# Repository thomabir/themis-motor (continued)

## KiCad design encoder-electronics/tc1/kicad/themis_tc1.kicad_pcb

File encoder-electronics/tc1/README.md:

# Themis TC1

Goal: Figure out whether 10 kHz amplitude modulaiton works with the AD9834 DDS via the FS_ADJUST pin.

Secondary goal (optional): Have a minimal "sender" circuit for the encoder, test the differential driver

- Interfaces:
  - Power in: 4V lab PSU, ±13V lab PSU
  - Signal out: differential amplified DDS signal, can power the existing encoder coils
  - Digital IO: Every useful digital pin from the DDS is accessible via a pin header, for easy debugging
  - Testpoints: Every single analog signal is accessible, and jumpers between main sections are used for easy disconnecting of blocks.

- Strategy
  - Passives: Use 0Ωs and DNPs to keep it flexible. 0805 everything for easy modification by hand.
  - Using screw terminals for power and encoder, pin headers for digital. Not fancy, but cheap and quick.

- Power:
  - ±12 V: LT3097
    - 10 CHF/pc (= 5 CHF/rail)
    - 500 mA bipolar adjustable ultra-low-noise LDO
    - It's the best. Slightly pricy, but just works, no fuss.
    - Basically excludes LDOs as a noise source -> faster prototyping.
    - (Hurts a bit to buy fancy parts for a prototype)
  - 3.3 V: MAX8887
    - I've used it before -> copy-paste design
    - Decently low-noise
- DDS: AD9834
  - The big unknown: Can it modulate quickly and with low noise?
  - Does the differential output work as expected?
  - How to program it? Will figure out once I get it
- Clock: Active crystal oscillator at 75 MHz
- Diff-amp to drive encoder: AD8390
  - Lots of power, cheap, fast
  - Unknown: Made for ADSL, let's see if this works well in this application? Spec wise, it should work.

## How to run

Upload code to Teensy: `~/.platformio/penv/bin/pio run -e teensy41 -t upload`

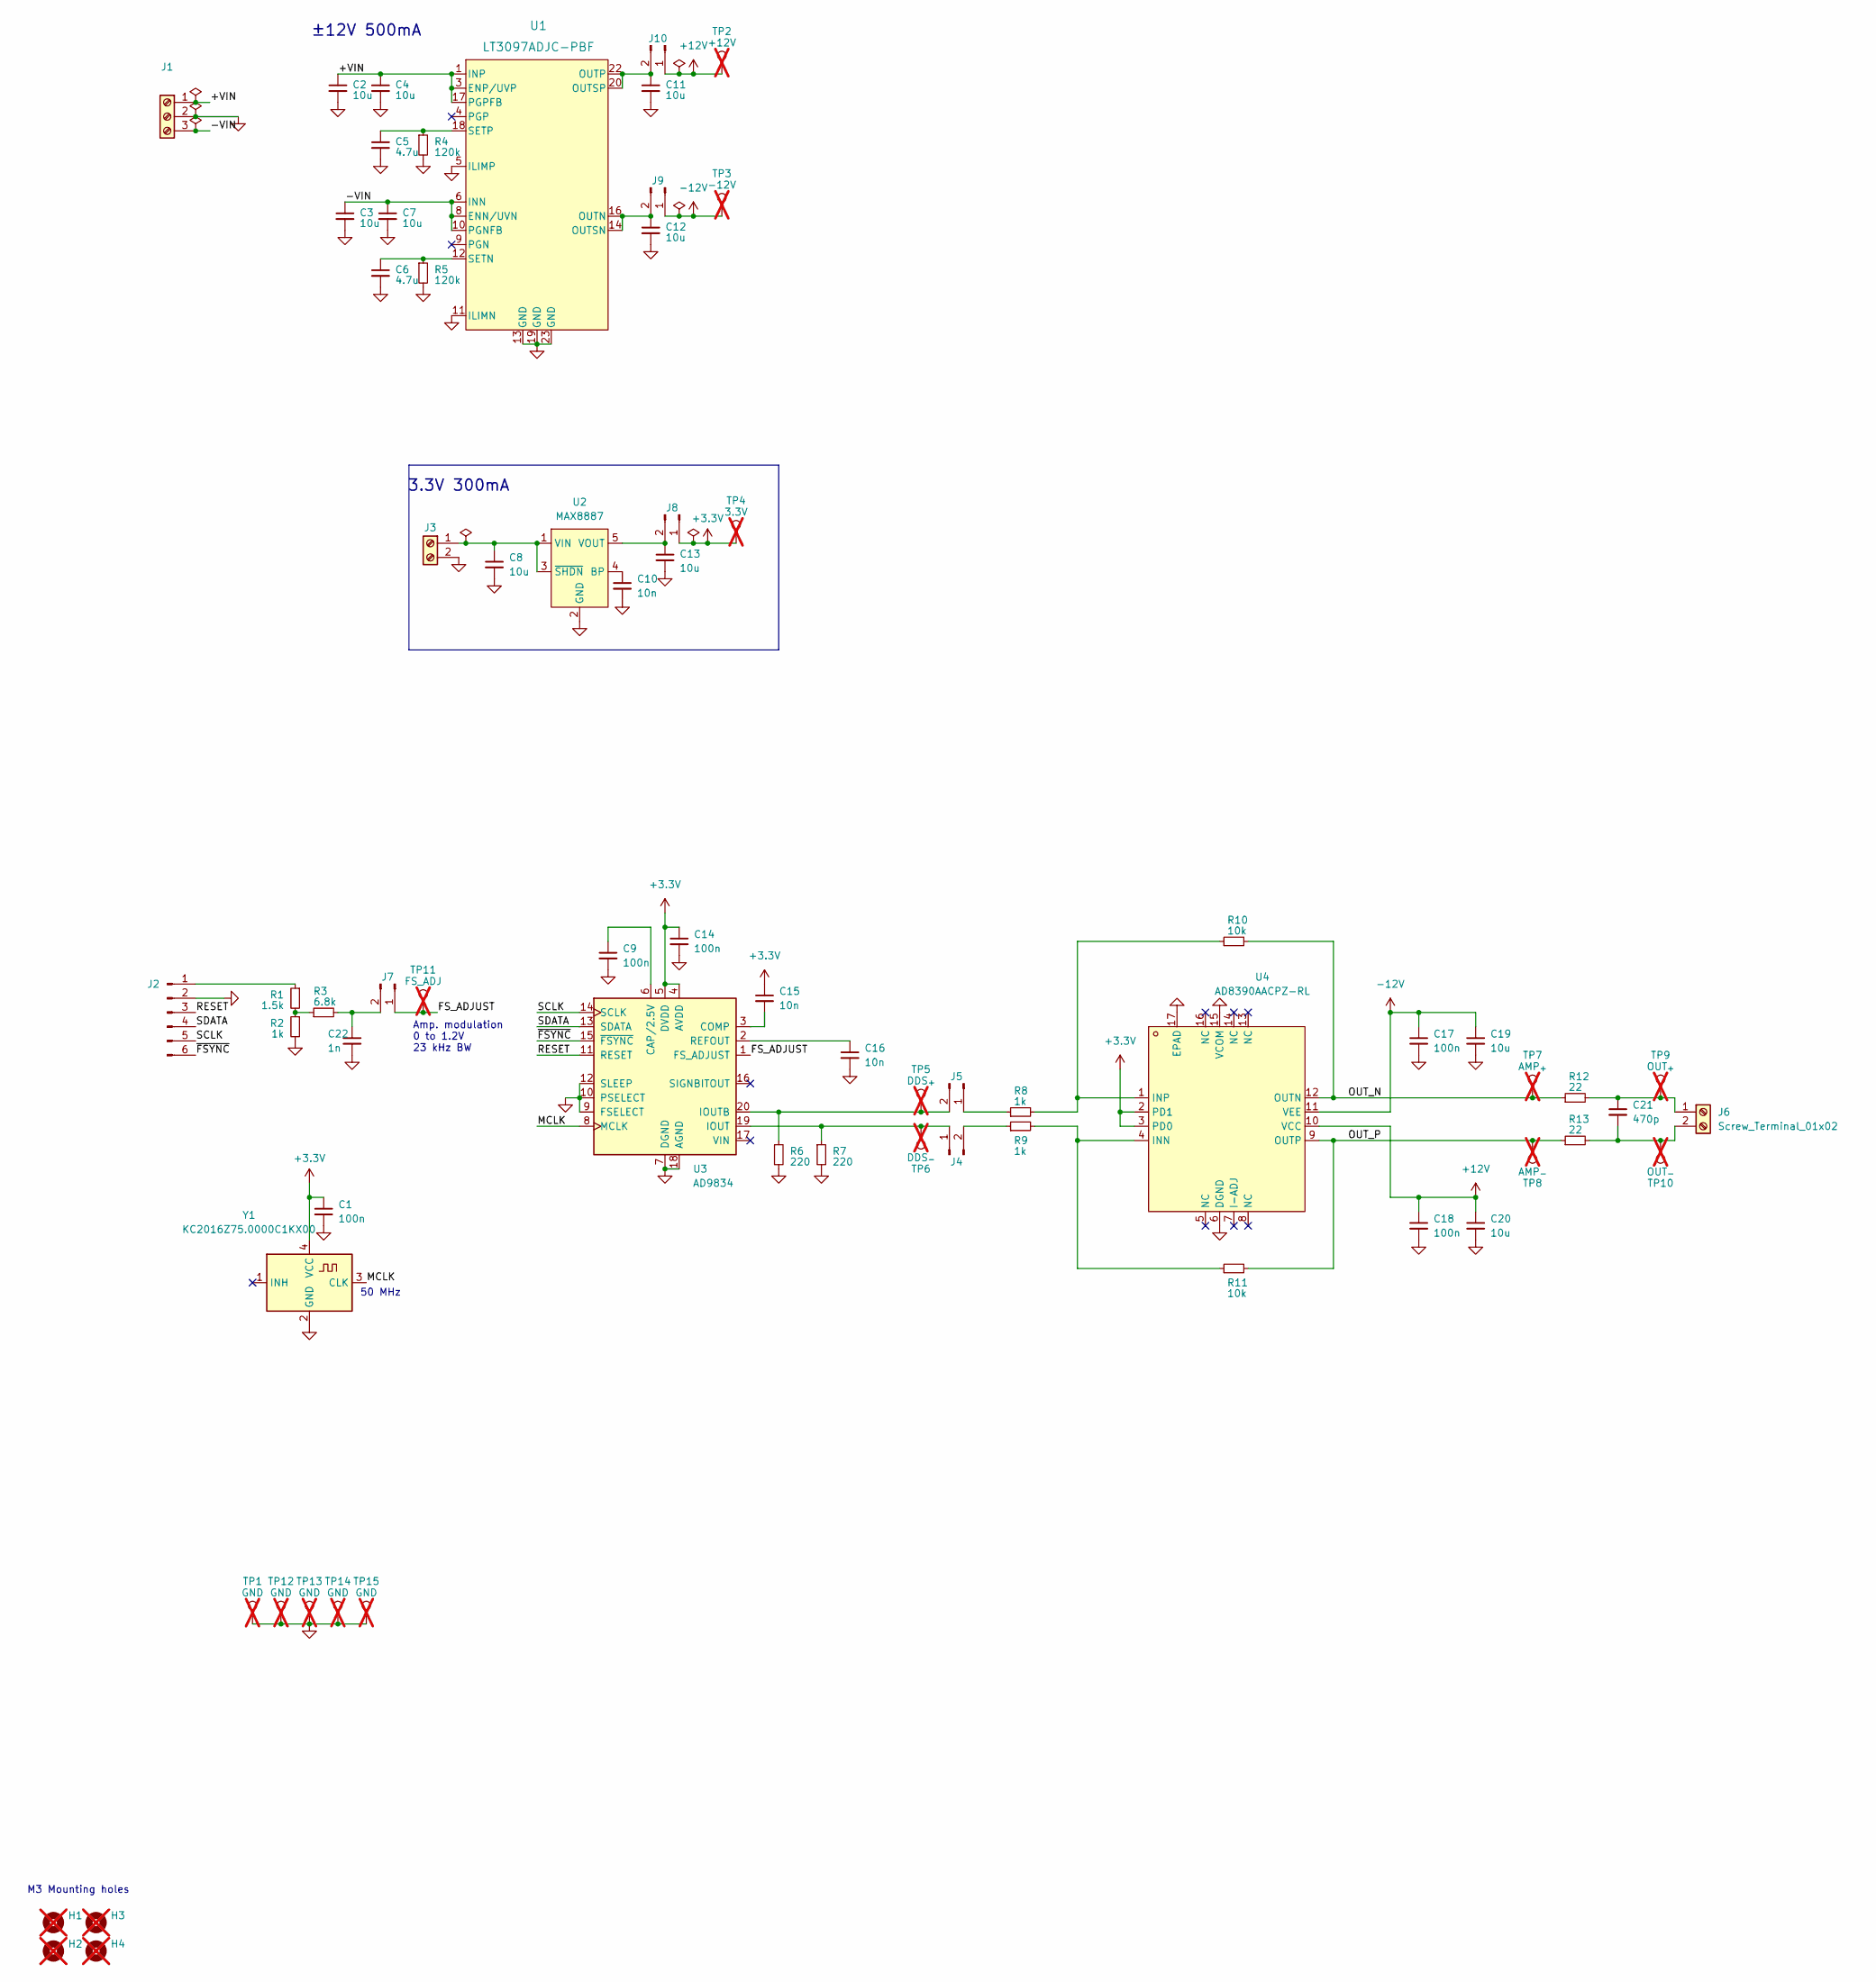
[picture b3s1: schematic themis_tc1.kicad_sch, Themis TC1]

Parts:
C1, C9, C14, C17, C18: 100n; C_0805_2012Metric
C2, C3, C4, C7, C8, C11, C12, C13, C19, C20: 10u; C_0805_2012Metric
C5, C6: 4.7u; C_0805_2012Metric
C10, C15, C16: 10n; C_0805_2012Metric
C21: 470p; C_0805_2012Metric
C22: 1n; C_0805_2012Metric
H1, H2, H3, H4: MountingHole; MountingHole_3.2mm_M3_DIN965; not fitted
J1: Screw_Terminal_01x03; TerminalBlock_TE_282834-3_1x03_P2.54mm_Horizontal
J2: Conn_01x06_Pin; PinHeader_1x06_P2.54mm_Vertical
J3: Screw_Terminal_01x02; TerminalBlock_TE_282834-2_1x02_P2.54mm_Horizontal; MPN 282834-2
J4, J5, J7, J8, J9, J10: Conn_01x02_Pin; PinHeader_1x02_P2.54mm_Vertical
J6: Screw_Terminal_01x02; TerminalBlock_TE_282834-2_1x02_P2.54mm_Horizontal
R1: 1.5k; R_0805_2012Metric
R2, R8, R9: 1k; R_0805_2012Metric
R3: 6.8k; R_0805_2012Metric
R4, R5: 120k; R_0805_2012Metric
R6, R7: 220; R_0805_2012Metric
R10, R11: 10k; R_0805_2012Metric
R12, R13: 22; R_0805_2012Metric
TP1, TP12, TP13, TP14, TP15: GND; TestPoint_Keystone_5010-5014_Multipurpose; not fitted
TP2: +12V; TestPoint_Keystone_5010-5014_Multipurpose; not fitted
TP3: -12V; TestPoint_Keystone_5010-5014_Multipurpose; not fitted
TP4: 3.3V; TestPoint_Keystone_5010-5014_Multipurpose; not fitted
TP5: DDS_{+}; TestPoint_Keystone_5010-5014_Multipurpose; not fitted
TP6: DDS_{-}; TestPoint_Keystone_5010-5014_Multipurpose; not fitted
TP7: AMP_{+}; TestPoint_Keystone_5010-5014_Multipurpose; not fitted
TP8: AMP_{-}; TestPoint_Keystone_5010-5014_Multipurpose; not fitted
TP9: OUT_{+}; TestPoint_Keystone_5010-5014_Multipurpose; not fitted
TP10: OUT_{-}; TestPoint_Keystone_5010-5014_Multipurpose; not fitted
TP11: FS_ADJ; TestPoint_Keystone_5010-5014_Multipurpose; not fitted
U1: LT3097ADJC-PBF; 05-08-7071_ADI
U2: MAX8887; SOT-23-5; MPN MAX8887
U3: AD9834; TSSOP-20_4.4x6.5mm_P0.65mm
U4: AD8390AACPZ-RL; LFCSP-16_L4.0-W4.0-P0.65-TL-EP2.0; LCSC Part C652757
Y1: KC2016Z75.0000C1KX00; Crystal_SMD_2016-4Pin_2.0x1.6mm

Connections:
+3.3V: C1.1, C14.1, C15.1, J8.1, TP4.1, U3.4 (AVDD), U3.5 (DVDD), U4.2 (PD1), U4.3 (PD0), Y1.4 (VCC)
+12V: C18.1, C20.1, J10.1, TP2.1, U4.10 (VCC)
-12V: C17.1, C19.1, J9.1, TP3.1, U4.11 (VEE)
/FS_ADJUST: J7.1, TP11.1, U3.1 (FS_ADJUST)
/MCLK: U3.8 (MCLK), Y1.3 (CLK)
/OUT_N: R10.2, R12.1, TP7.1, U4.12 (OUTN)
/OUT_P: R11.2, R13.1, TP8.1, U4.9 (OUTP)
/RESET: J2.3, U3.11 (RESET)
/SCLK: J2.5, U3.14 (SCLK)
/SDATA: J2.4, U3.13 (SDATA)
/~FSYNC: J2.6, U3.15 (~FSYNC)
GND: C1.2, C2.2, C3.2, C4.2, C5.2, C6.2, C7.2, C8.2, C9.2, C10.2, C11.2, C12.2, C13.2, C14.2, C16.2, C17.2, C18.2, C19.2, C20.2, C22.2, J1.2, J2.2, J3.2, R2.2, R4.2, R5.2, R6.2, R7.2, TP1.1, TP12.1, TP13.1, TP14.1, TP15.1, U1.5 (ILIMP), U1.11 (ILIMN), U1.13 (GND), U1.19 (GND), U1.23 (GND), U2.2 (GND), U3.7 (DGND), U3.9 (FSELECT), U3.10 (PSELECT), U3.12 (SLEEP), U3.18 (AGND), U4.6 (DGND), U4.15 (VCOM), U4.17 (EPAD), Y1.2 (GND)
INN: C3.1, C7.1, J1.3, U1.6 (INN), U1.7 (INN), U1.8 (ENN/UVN), U1.10 (PGNFB), U1.24 (INN)
INP: C2.1, C4.1, J1.1, U1.1 (INP), U1.2 (INP), U1.3 (ENP/UVP), U1.17 (PGPFB)
unnamed: J2.1, R1.1
unnamed: C8.1, J3.1, U2.1 (VIN), U2.3 (~SHDN)
unnamed: J4.1, R7.1, TP6.1, U3.19 (IOUT)
unnamed: J4.2, R9.1
unnamed: J5.1, R8.1
unnamed: J5.2, R6.1, TP5.1, U3.20 (IOUTB)
unnamed: C21.1, J6.1, R12.2, TP9.1
unnamed: C21.2, J6.2, R13.2, TP10.1
unnamed: C22.1, J7.2, R3.2
unnamed: C13.1, J8.2, U2.5 (VOUT)
unnamed: C12.1, J9.2, U1.14 (OUTSN), U1.15 (OUTN), U1.16 (OUTN)
unnamed: C11.1, J10.2, U1.20 (OUTSP), U1.21 (OUTP), U1.22 (OUTP)
unnamed: R1.2, R2.1, R3.1
unnamed: C6.1, R5.1, U1.12 (SETN)
unnamed: C5.1, R4.1, U1.18 (SETP)
unnamed: C10.1, U2.4 (BP)
unnamed: C9.1, U3.6 (CAP/2.5V)
unnamed: C15.2, U3.3 (COMP)
unnamed: C16.1, U3.2 (REFOUT)
unnamed: R9.2, R11.1, U4.4 (INN)
unnamed: R8.2, R10.1, U4.1 (INP)

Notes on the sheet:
M3 Mounting holes
50 MHz
Amp. modulation 0 to 1.2V 23 kHz BW
3.3V 300mA
±12V 500mA

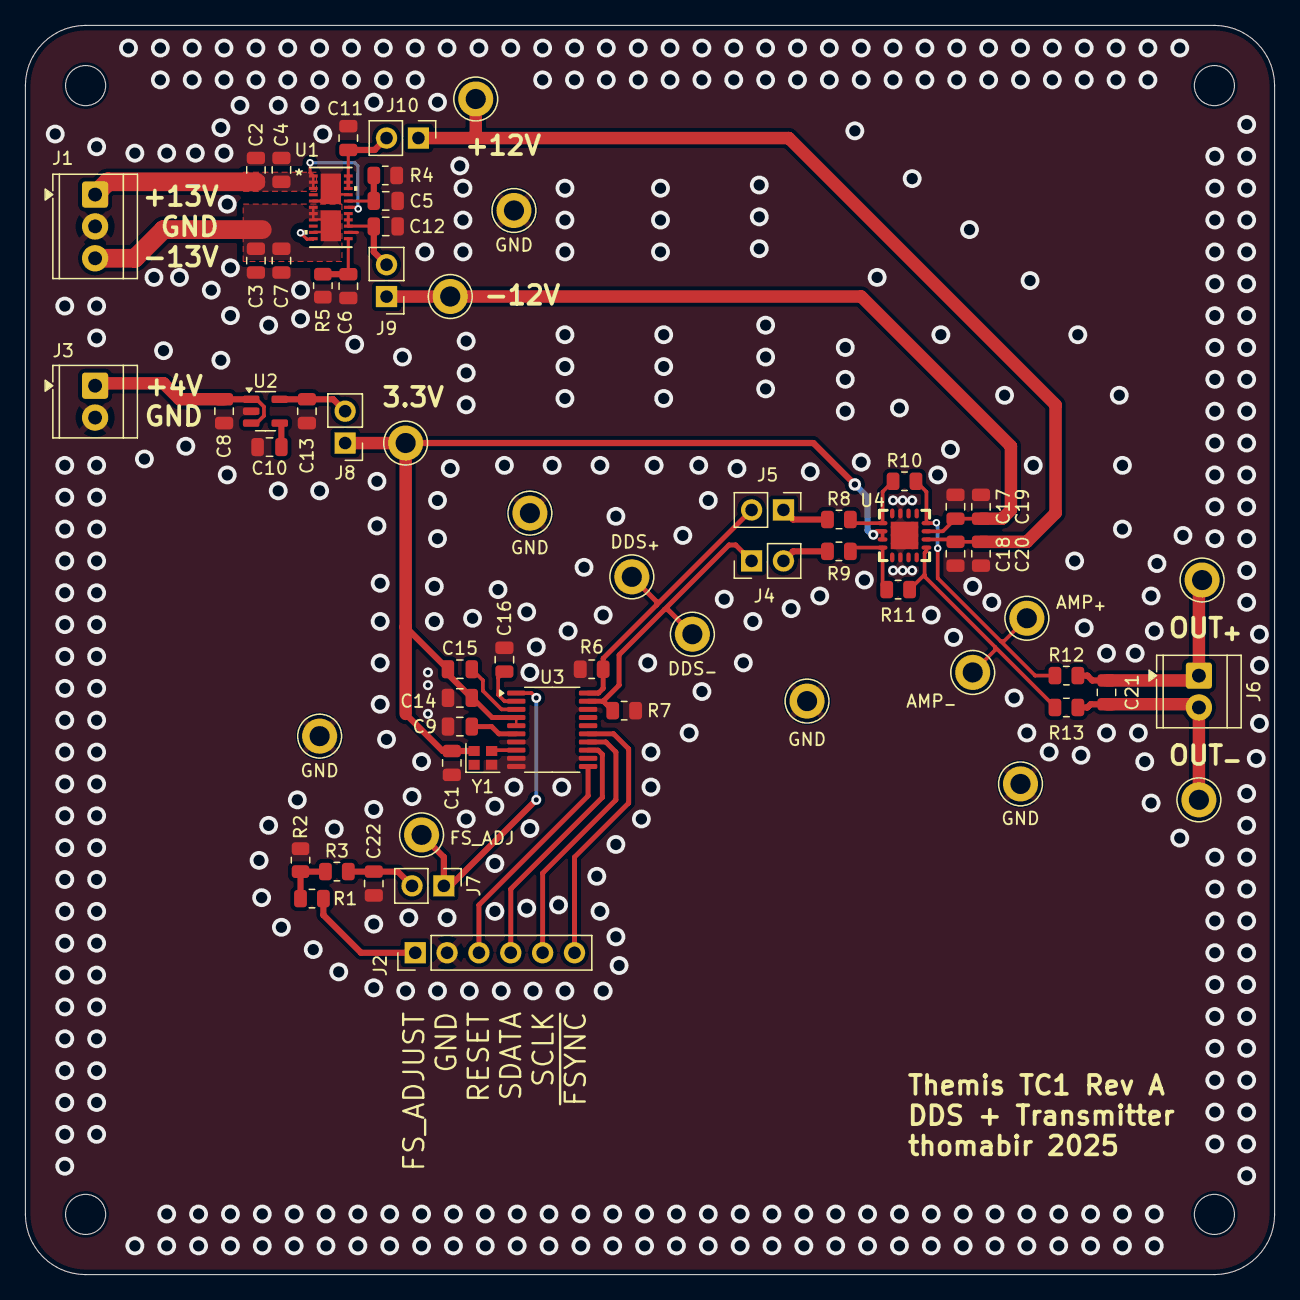
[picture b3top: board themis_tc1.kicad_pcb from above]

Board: 4 copper layers, 99.6 x 99.6 mm, 69 parts (0 on the bottom side), 35 nets.

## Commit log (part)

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2026-01-04 TC1 (DDS) Rev. A
2026-01-04 TC2 (RX) Rev. A
2026-01-05 Generate iBOM for TC1
2026-01-05 Generate iBOM for TC2
2026-01-05 Add sim for TC2
2026-04-18 2026-04-18
2026-04-20 TC1 bringup: AD9834 DDS producing 1 MHz sine wave
    - Fix MCLK_HZ: oscillator is 75 MHz (BOM was correct, schematic was wrong)
    - Fix root cause of silent DDS: RESET pin was floating, holding chip in
    reset. Drive RESET LOW before initialising DDS, and construct AD9834
    object inside setup() so SPI is ready.
    - Add teensy-cli upload protocol to platformio.ini
    - Add AD9834 Arduino library (modified from AliBarber/AD9834)
2026-04-20 TC1 bringup: Differential amplifier working at 1 MHz
2026-04-21 Implement interactive serial interface with amp and freq control
2026-04-21 Add .claude/ to gitignore
2026-04-22 Add maths for amplitude on FS_ADJUST
2026-04-22 tc1: add corrected amplitude command 'ac' (0–100)
2026-04-22 tc1: extract serial command parsing into header-only cmd_parser.hpp
2026-04-22 tc1: add amplitude modulation with DdsController interface
    Introduce sinusoidal AM on the FS_ADJUST carrier amplitude:
    - New AmplitudeModulator: IntervalTimer ISR at 200 kHz drives FS_ADJUST PWM;
    modulation math a(t) = carrier*(1 + index*cos(acc + phase)) in the ISR.
    - New DdsController: hardware interface boundary that owns AD9834 +
    AmplitudeModulator. main.cpp and CmdParser no longer include AD9834.h
    directly — swapping the DDS IC only requires updating dds_controller.hpp.
